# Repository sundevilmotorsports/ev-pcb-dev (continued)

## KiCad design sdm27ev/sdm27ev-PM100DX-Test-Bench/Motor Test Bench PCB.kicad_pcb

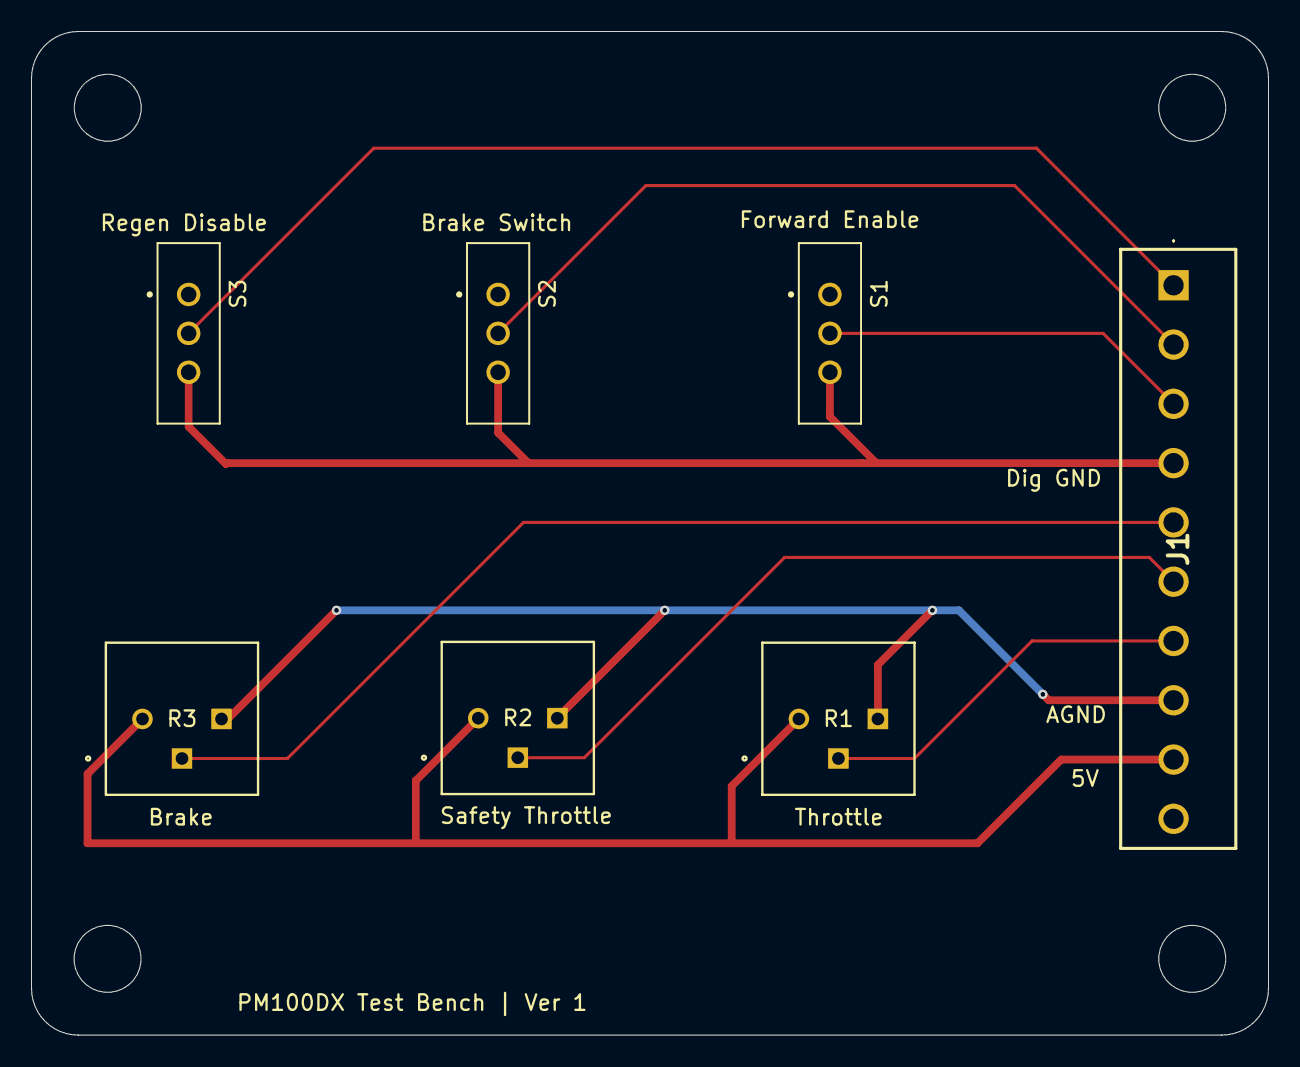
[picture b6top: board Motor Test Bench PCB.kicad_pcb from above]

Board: 2 copper layers, 79.5 x 64.5 mm, 7 parts (0 on the bottom side), 9 nets.

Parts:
J1: 20020327-D101B01LF; 20020327D101B01LF
R1: Throttle; POT_3386P
R2: Safety Throttle; POT_3386P
R3: Brake; POT_3386P
S1: Forward Enable; SW_EG1218
S2: Brake Switch; SW_EG1218
S3: Regen Disable; SW_EG1218

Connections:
5V: J1.9, R1.1, R2.1, R3.1
AGND: J1.8, R1.3, R2.3, R3.3
Brake Signal: J1.5, R3.2
Brake Switch: J1.2, S2.2
Digintal GND: J1.4, S1.3, S2.3, S3.3
Forward Enable: J1.3, S1.2
Regen Disable: J1.1, S3.2
Safety Throttle Signal: J1.6, R2.2
Throttle Signal: J1.7, R1.2

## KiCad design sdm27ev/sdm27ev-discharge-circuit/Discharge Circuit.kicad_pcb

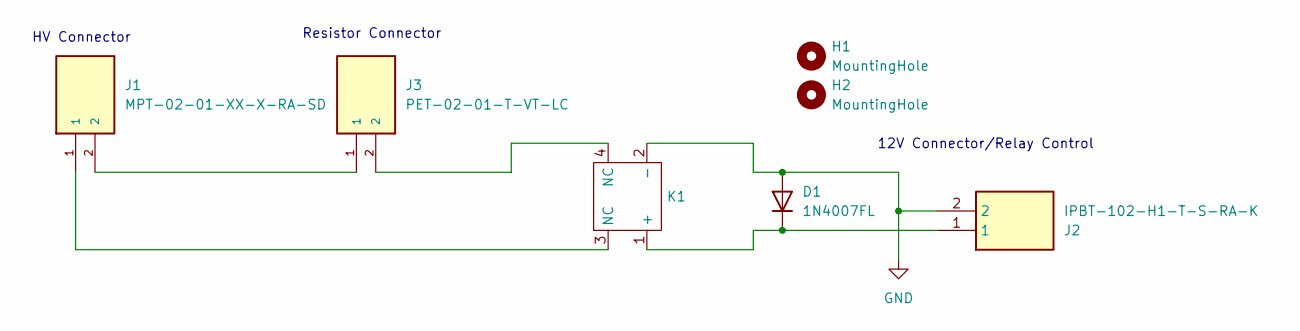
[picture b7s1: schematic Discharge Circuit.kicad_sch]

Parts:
D1: 1N4007FL; D_SOD-123F
H1, H2: MountingHole; MountingHole_3.2mm_M3
J1: MPT-02-01-XX-X-RA-SD; SAMTEC_MPT-02-01-XX-X-RA-SD; PARTREV B
J2: IPBT-102-H1-T-S-RA-K; IPBT102H1TSRAK; Mouser Part Number 200-IPBT102H1TSRAK
J3: PET-02-01-T-VT-LC; SAMTEC_PET-02-XX-X-VT-LC; PARTREV C
K1: S82405VHR

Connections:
GND: D1.2 (A), J2.2, K1.2 (-)
unnamed: D1.1 (K), J2.1, K1.1 (+)
unnamed: J1.1, K1.3 (NC)
unnamed: J1.2, J3.1
unnamed: J3.2, K1.4 (NC)

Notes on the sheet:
Resistor Connector
12V Connector/Relay Control
HV Connector

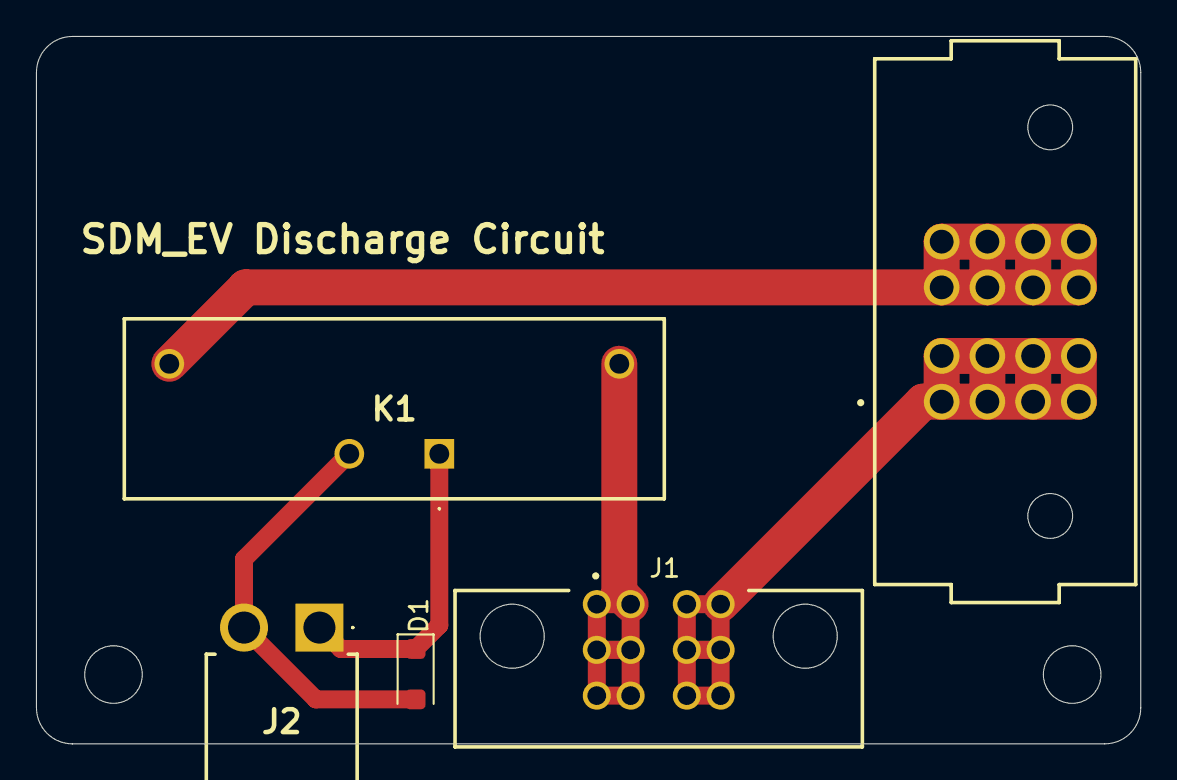
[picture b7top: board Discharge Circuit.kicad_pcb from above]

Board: 2 copper layers, 61.3 x 39.3 mm, 7 parts (0 on the bottom side), 5 nets.

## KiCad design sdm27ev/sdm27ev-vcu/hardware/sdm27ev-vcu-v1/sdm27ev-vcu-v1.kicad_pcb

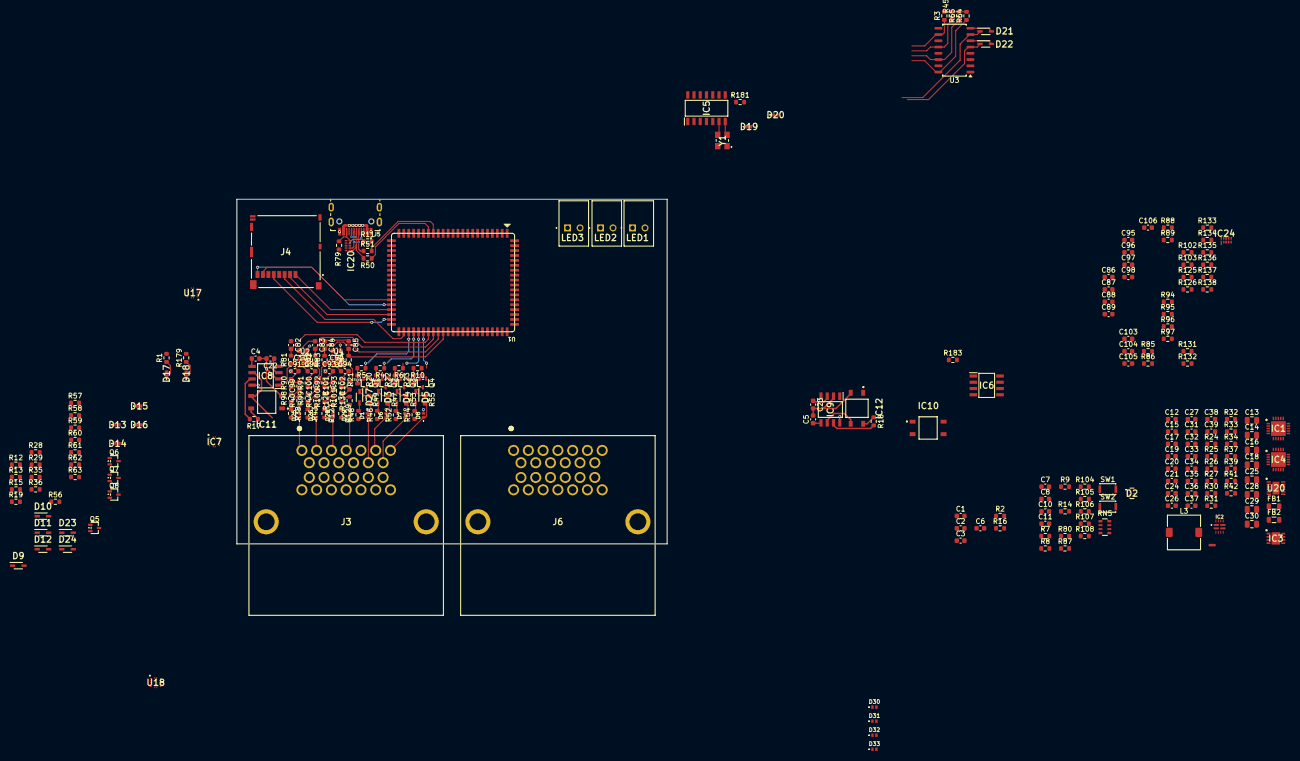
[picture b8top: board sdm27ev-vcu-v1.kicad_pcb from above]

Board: 2 copper layers, 87.4 x 70.0 mm, 253 parts (0 on the bottom side), 181 nets.

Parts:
C1, C2, C3, C4, C5, C6, C7, C11, C15, C17, C22, C23, C24, C26, C32, C34, C82, C83, C84, C85, C86, C87, C88, C89, C90, C107: 100nF; C_0603_1608Metric
C8, C19, C20, C21, C31, C33, C35, C36, C37, C38, C39: 1uF; C_0603_1608Metric
C10: 10uF; C_0603_1608Metric
C12: 10nF; C_0603_1608Metric
C13, C14, C16, C18: 10uF; C_0805_2012Metric
C25, C28: 4.7uF; C_0805_2012Metric
C27: 33pF; C_0603_1608Metric
C29, C30: 33uF; C_0805_2012Metric
C91, C92, C93, C94, C95, C96, C97, C98: 10n; C_0603_1608Metric
C99, C100, C101, C102, C103, C104, C105, C106: 20.5nF; C_0603_1608Metric
D1, D6, D7, D8, D25, D26, D28, D29, D30, D31, D32, D33: PESD24VL1BLS-QYL; PESD24VL1BLSQYL-Compact
D2: PUSB3FR6Z
D3, D4, D5, D9, D10, D11, D12, D21, D22, D23, D24, D27: BAT54WS-7-F; SOD2513X120N
D13, D14, D15, D16, D17, D18, D19, D20: PESD24VL1BLS-QYL; PESD24VL1BLSQYL
FB1, FB2: 600Ohm@100MHz ~1.4A; L_0805_2012Metric
IC1, IC4: MAX20087ATPB_VY+T; QFN50P400X400X80-21N-D
IC2: TPS2121RUXR
IC3: TLV76733QWDRBRQ1; SON65P300X300X100-9N-D
IC5: MCP2518FDT-E_SL; SOIC127P600X175-14N
IC6, IC8, IC9: TCAN3413DR; SOIC127P600X175-8N
IC7: TLV9064IRUCR; QFN40P200X200X40-14N
IC10, IC11, IC12: TLP175A_TPL,E; TLP266J
IC20, IC24: TPD4E05U06QDQARQ1; DQA_R-PUSON-N10_
J3, J6: 6437288-4; 64372884
J4: 2201778-1; 22017781
J5: USB4725-03-C-KIT; GCT_USB4730-GF-A_REVA
L3: 4.7uH; L_SXN_SMDRI62
LED1: RED; SSFLXH100LID01
LED2, LED3: GREEN; SSFLXH100LID01
NT1: NetTieGND; NetTie-2_SMD_Pad0.5mm
Q1, Q2, Q3, Q4, Q5, Q6, Q7, Q8: DMN62D2UWQ; SOT-323_SC-70
R1, R42, R46, R47, R48, R49, R52, R53, R54, R55, R56, R57, R58, R59, R60, R61, R62, R63, R179, R181, R183: 1k; R_0603_1608Metric
R2: 0; R_0603_1608Metric
R3, R45, R64, R65: 10K; R_0603_1608Metric
R4, R5, R6, R10, R12, R13, R15, R16, R17, R18, R19, R81, R82, R83, R84, R85, R86, R88, R89, R106, R107, R108: 100; R_0603_1608Metric
R7, R8, R9, R14, R38, R43, R80, R87, R104, R105, R127, R129, R131, R133, R135, R137: 10k; R_0603_1608Metric
R11, R79: 5.1k; R_0603_1608Metric
R20, R21, R22, R23, R28, R29, R35, R36, R41: 100k; R_0603_1608Metric
R24: 16.2; R_0603_1608Metric
R25, R27, R31: 5k; R_0603_1608Metric
R26, R30: 21k; R_0603_1608Metric
R32: 24.2k; R_0603_1608Metric
R33, R34: 25k; R_0603_1608Metric
R37: 34.8k; R_0603_1608Metric
R39: 19.1k; R_0603_1608Metric
R40, R44, R128, R130, R132, R134, R136, R138: 17.8K; R_0603_1608Metric
R50, R51: 27; R_0603_1608Metric
R90, R91, R92, R93, R94, R95, R96, R97: 6.49k; R_0603_1608Metric
R98, R99, R100, R101, R102, R103, R125, R126: 4.75k; R_0603_1608Metric
RN5: 10k; R_Array_Convex_4x0603
SW1, SW2: SW_Push; SW_SPST_CK_KXT3
U1: WT0132P4-A1
U2, U4: TLV9062xDSG; WSON-8-1EP_2x2mm_P0.5mm_EP0.9x1.6mm_ThermalVias
U3: TLP293-4; SOIC-16_4.55x10.3mm_P1.27mm
U17, U18: TLV9064IRUCR; QFN40P200X200X40-14N
U20: LMR51450FSQDRRRQ1; SON50P300X300X80-13N-D
Y1: ECS-3225MVQ-400-BS-TR; ECS3225MVQ400BSTR

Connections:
3.3V: C1.1, C2.1, C6.1, C7.1, C8.1, C13.1, C22.1, C23.1, C32.1, C34.1, FB1.1, IC1.11 (VDD), IC1.15 (EN), IC3.1 (OUT), IC3.3 (SNS), IC4.11 (VDD), IC4.15 (EN), IC4.16 (ADDR), IC5.14 (VDD), IC6.3 (VCC), IC8.3 (VCC), IC9.3 (VCC), J4.4 (VDD), R3.2, R7.2, R8.2, R9.2, R14.1, R45.2, R64.2, R65.2, R87.2, R104.2, R105.1, R106.1, R107.2, R108.2, Y1.1 (TRI-STATE), Y1.4 (VDD)
5V: C29.1, C30.1, FB2.1, IC2.7 (IN1), L3.2, R24.2, R26.2, R41.2, R42.2
12V: C25.1, C26.1, C28.1, R46.1, R48.1, R52.1, R54.1, R56.1, R57.1, R58.1, R59.1, U20.9 (EN), U20.10 (VIN), U20.11 (VIN_2), U20.12 (VIN_3)
/A1: C86.2, R85.2, U1.74 (GPIO16)
/A1IN: D25.1, J3.1, R38.2
/A2: C87.2, R86.2, U1.75 (GPIO17)
/A2IN: D26.1, J3.2, R43.2
/A3: C88.2, R88.2, U1.76 (GPIO18)
/A3IN: D28.1, J3.3, R127.2
/A4: C89.2, R89.2, U1.77 (GPIO19)
/A4IN: D29.1, J3.4, R129.2
/A5: C82.2, R81.2, U1.48 (GPIO49)
/A5IN: D30.1, IC24.1 (A5), R131.2
/A6: C83.2, R82.2, U1.49 (GPIO50)
/A6IN: D31.1, IC24.2 (A6), R133.2
/A7: C84.2, R83.2, U1.50 (GPIO51)
/A7IN: D32.1, IC24.4 (A7), R135.2
/A8: C85.2, R84.2, U1.51 (GPIO52)
/A8IN: D33.1, IC24.5 (A8), R137.2
/CAN1+: IC6.7 (CANH), R16.2
/CAN1-: IC6.6 (CANL), IC10.4
/CAN1_TERM: IC10.1, U1.72 (GPIO1)
/CAN2+: IC8.7 (CANH), R17.2
/CAN2-: IC8.6 (CANL), IC11.4
/CAN2_RX: IC8.4 (RXD), U1.52 (GPIO53)
/CAN2_TERM: IC11.1, U1.55 (GPIO2)
/CAN2_TX: IC8.1 (TXD), U1.54 (GPIO54)
/CAN3+: IC9.7 (CANH), R18.2
/CAN3-: IC9.6 (CANL), IC12.4
/CAN3_RX: IC9.4 (RXD), U1.65 (GPIO11)
/CAN3_TERM: IC12.1, U1.56 (GPIO3)
/CAN3_TX: IC9.1 (TXD), U1.63 (GPIO10)
/CAN/CAN1_RX: IC5.2 (RXCAN), IC6.4 (RXD)
/CAN/CAN1_STB: IC5.9 (~INT0/GPIO0/XSTBY), IC6.8 (STB), R2.2
/CAN/CAN1_TX: IC5.1 (TXCAN), IC6.1 (TXD)
/CAN_INT_1: IC5.4 (~INT), R14.2, U1.71 (GPIO0)
/CAN_SPI2_CS1: IC5.13 (NCS), U1.57 (GPIO4)
/CAN_SPI2_SCK: IC5.10 (SCK), U1.59 (GPIO6)
/CAN_SPI2_SDI: IC5.11 (SDI), U1.60 (GPIO7)
/CAN_SPI2_SDO: IC5.12 (SDO), U1.58 (GPIO5)
/DI1: R3.1, U1.69 (GPIO15), U3.10
/DI1IN: D17.1, R1.1
/DI2: R45.1, U1.68 (GPIO14), U3.12
/DI2IN: D18.1, R179.1
/DI3: R64.1, U1.66 (GPIO12), U3.16
/DI3IN: D19.1, R181.1
/DI4: R65.1, U1.67 (GPIO13), U3.14
/DI4IN: D20.1, R183.1
/DO1: R5.1, U1.44 (GPIO45)
/DO1IN: D1.1, J3.12, R49.2
/DO2: R4.1, U1.45 (GPIO46)
/DO2IN: D6.1, J3.6, R47.2
/DO3: R6.1, U1.46 (GPIO47)
/DO3IN: D7.1, J3.13, R53.2
/DO4: R10.1, U1.47 (GPIO48)
/DO4IN: D8.1, J3.7, R55.2
/DO5: R12.1, U1.24 (GPIO28)
/DO5IN: D13.1, R60.2
/DO6: R13.1, U1.25 (GPIO29)
/DO6IN: D14.1, R61.2
/DO7: R15.1, U1.26 (GPIO30)
/DO7IN: D15.1, R62.2
/DO8: R19.1, U1.27 (GPIO31)
/DO8IN: D16.1, R63.2
/ESP_LDO: R80.2, RN5.5 (R4.2), RN5.6 (R3.2), RN5.7 (R2.2), RN5.8 (R1.2), U1.32 (ESP_LDO_VO4)
/Power/A1_5V: C31.1, IC1.6 (OUT1)
/Power/A2_5V: C21.1, IC1.20 (OUT2)
/Power/A3_5V: C20.1, IC1.7 (OUT3)
/Power/A4_5V: C19.1, IC1.19 (OUT4)
/Power/A5_5V: C39.1, IC4.6 (OUT1)
/Power/A6_5V: C38.1, IC4.20 (OUT2)
/Power/A7_5V: C37.1, IC4.7 (OUT3)
/Power/A8_5V: C36.1, IC4.19 (OUT4)
/Power/SCL: IC1.14 (SCL), IC4.14 (SCL)
/Power/SDA: IC1.13 (SDA), IC4.13 (SDA)
/SD1-CLK: D2.4 (CLK), J4.5 (CLK), U1.40 (GPIO43)
/SD1-CMD: D2.5 (CMD), J4.3 (CMD), R80.1, U1.43 (GPIO44)
/SD1-DAT0: D2.1 (DAT0), J4.7 (DAT0), RN5.4 (R4.1), U1.36 (GPIO39)
/SD1-DAT1: D2.7 (DAT1), J4.8 (DAT1), RN5.3 (R3.1), U1.37 (GPIO40)
/SD1-DAT2: D2.6 (DAT2), J4.1 (DAT2), RN5.2 (R2.1), U1.38 (GPIO41)
/SD1-DAT3: D2.3 (DAT3), J4.2 (CD/DAT3), RN5.1 (R1.1), U1.39 (GPIO42)
/StatLED1: LED3.1 (K), U1.28 (GPIO32)
/StatLED2: LED2.1 (K), U1.29 (GPIO33)
/USB_D+: IC20.1 (A1), J5.A6 (D+), J5.B6 (D+), R50.2
/USB_D-: IC20.2 (A2), J5.A7 (D-), J5.B7 (D-), R51.1
A3.3V: C15.1, C16.1, C90.1, C107.1, FB1.2, U2.8 (V+), U4.8 (V+), U17.3 (V+), U18.3 (V+)
A5V: C17.1, C18.1, C33.1, C35.1, FB2.2, IC1.2 (IN), IC1.3 (IN_2), IC1.4 (IN_3), IC4.2 (IN), IC4.3 (IN_2), IC4.4 (IN_3)
GND: C1.2, C2.2, C3.2, C4.2, C5.2, C6.2, C7.2, C8.2, C10.2, C11.2, C12.2, C13.2, C14.2, C15.2, C16.2, C17.2, C18.2, C19.2, C20.2, C21.2, C22.2, C23.2, C25.2, C26.2, C28.2, C29.2, C30.2, C31.2, C32.2, C33.2, C34.2, C35.2, C36.2, C37.2, C38.2, C39.2, C82.1, C83.1, C84.1, C85.1, C86.1, C87.1, C88.1, C89.1, C90.2, C91.1, C92.1, C93.1, C94.1, C95.1, C96.1, C97.1, C98.1, C107.2, D1.2, D2.2 (GND), D6.2, D7.2, D8.2, D13.2, D14.2, D15.2, D16.2, D17.2, D18.2, D19.2, D20.2, D21.2 (A), D22.2 (A), D23.2 (A), D24.2 (A), D25.2, D26.2, D28.2, D29.2, D30.2, D31.2, D32.2, D33.2, IC1.1 (PGND_1), IC1.5 (PGND_2), IC1.9 (GND), IC1.12 (GND_2), IC1.16 (ADDR), IC1.21 (EP), IC2.3 (CP2), IC2.9 (ST), IC2.12 (GND), IC3.4 (GND), IC3.6 (GND_2), IC3.9 (EP), IC4.1 (PGND_1), IC4.5 (PGND_2), IC4.9 (GND), IC4.12 (GND_2), IC4.21 (EP), IC5.7 (VSS), IC6.2 (GND), IC8.2 (GND), IC8.8 (STB), IC9.2 (GND), IC9.8 (STB), IC10.3, IC11.3, IC12.3, IC20.3 (GND), IC20.8 (GND_2), IC24.3 (GND), IC24.8 (GND_2), J3.5, J3.9, J3.11, J4.6 (VSS), J4.11 (GND_1), J4.12 (GND_2), J4.13 (GND_3), J4.14 (GND_4), J4.15 (GND_5), J4.16 (GND_6), J5.A1 (GND), LED1.1 (K), NT1.1, Q1.2 (S), Q2.2 (S), Q3.2 (S), Q4.2 (S), Q5.2 (S), Q6.2 (S), Q7.2 (S), Q8.2 (S), R2.1, R11.2, R20.1, R21.1, R22.1, R23.1, R25.1, R27.1, R28.1, R29.1, R31.1, R32.1, R33.1, R34.1, R35.1, R36.1, R37.1, R40.1, R44.1, R79.2, R128.1, R130.1, R132.1, R134.1, R136.1, R138.1, SW1.1, SW2.2, U1.1 (GND), U1.8 (GND), U1.15 (GND), U1.18 (GND), U1.21 (GND), U1.42 (GND), U1.53 (GND), U1.64 (GND), U1.73 (GND), U1.82 (GND), U2.4 (V-), U2.9 (PAD), U3.2, U3.4, U3.6, U3.8, U3.9, U3.11, U3.13, U3.15, U4.4 (V-), U4.9 (PAD), U17.10 (V-), U18.10 (V-), U20.13 (PGND), Y1.2 (GND)
unnamed: C27.2, R42.1
unnamed: C99.1, R90.1, R98.2
unnamed: C100.1, R91.1, R99.2
unnamed: C101.1, R92.1, R100.2
unnamed: C102.1, R93.1, R101.2
unnamed: C103.1, R94.1, R102.2
unnamed: C104.1, R95.1, R103.2
unnamed: C105.1, R96.1, R125.2
unnamed: C106.1, R97.1, R126.2
unnamed: D3.2 (A), R46.2
unnamed: D3.1 (K), Q2.3 (D), R47.1
unnamed: D4.2 (A), R52.2
unnamed: D4.1 (K), Q3.3 (D), R53.1
unnamed: D5.2 (A), R54.2
unnamed: D5.1 (K), Q4.3 (D), R55.1
unnamed: D9.2 (A), R56.2
unnamed: D9.1 (K), Q5.3 (D), R60.1
unnamed: D10.2 (A), R57.2
unnamed: D10.1 (K), Q6.3 (D), R61.1
unnamed: D11.2 (A), R58.2
unnamed: D11.1 (K), Q7.3 (D), R62.1
unnamed: D12.2 (A), R59.2
unnamed: D12.1 (K), Q8.3 (D), R63.1
unnamed: D21.1 (K), R1.2, U3.7
unnamed: D22.1 (K), R179.2, U3.5
unnamed: D23.1 (K), R181.2, U3.1
unnamed: D24.1 (K), R183.2, U3.3
unnamed: D27.2 (A), R48.2
unnamed: D27.1 (K), Q1.3 (D), R49.1
unnamed: IC1.10 (ISET), R33.2
unnamed: IC2.10 (ILIM), R32.2
unnamed: IC2.5 (OV1), R26.1, R27.2
unnamed: IC2.4 (OV2), R30.1, R31.2
unnamed: IC2.6 (PR1), R24.1, R25.2
unnamed: C12.1, IC2.11 (SS)
unnamed: IC4.10 (ISET), R34.2
unnamed: IC5.6 (OSC1), Y1.3 (OUTPUT)
unnamed: C3.1, IC6.5 (V_IO)
unnamed: C4.1, IC8.5 (V_IO)
unnamed: C5.1, IC9.5 (V_IO)
unnamed: IC10.6, R16.1
unnamed: IC11.6, R17.1
unnamed: IC12.6, R18.1
unnamed: IC20.4 (A3), J5.A5 (CC1), R11.1
unnamed: IC20.5 (A4), J5.B5 (CC2), R79.1
unnamed: IC20.6 (NC_4), IC20.7 (NC_1), IC20.9 (NC_2), IC20.10 (NC_3)
unnamed: IC24.6 (NC_4), IC24.7 (NC_1), IC24.9 (NC_2), IC24.10 (NC_3)
unnamed: LED1.2 (A), R106.2
unnamed: LED2.2 (A), R107.1
unnamed: LED3.2 (A), R108.1
unnamed: Q1.1 (G), R5.2, R21.2
unnamed: Q2.1 (G), R4.2, R20.2
unnamed: Q3.1 (G), R6.2, R22.2
unnamed: Q4.1 (G), R10.2, R23.2
unnamed: Q5.1 (G), R12.2, R28.2
unnamed: Q6.1 (G), R13.2, R29.2
unnamed: Q7.1 (G), R15.2, R35.2
unnamed: Q8.1 (G), R19.2, R36.2
unnamed: R38.1, R40.2, R98.1
unnamed: R43.1, R44.2, R99.1
unnamed: R100.1, R127.1, R128.2
unnamed: R101.1, R129.1, R130.2
unnamed: R102.1, R131.1, R132.2
unnamed: R103.1, R133.1, R134.2
unnamed: R125.1, R135.1, R136.2
unnamed: R126.1, R137.1, R138.2
unnamed: R8.1, R9.1, SW1.2, SW2.1, U1.31 (GPIO35), U1.70 (CHIP_PU)
unnamed: R7.1, U1.33 (GPIO36)
unnamed: R51.2, U1.16 (USB_DM)
unnamed: R50.1, U1.17 (USB_DP)
unnamed: C91.2, R90.2, U2.3 (+)
unnamed: C99.2, R81.1, U2.1, U2.2 (-)
unnamed: C92.2, R91.2, U2.5 (+)
unnamed: C100.2, R82.1, U2.6 (-), U2.7
unnamed: C93.2, R92.2, U4.3 (+)
unnamed: C101.2, R83.1, U4.1, U4.2 (-)
unnamed: C94.2, R93.2, U4.5 (+)
unnamed: C102.2, R84.1, U4.6 (-), U4.7
unnamed: C95.2, R94.2, U18.1 (IN1+)
unnamed: C103.2, R85.1, U18.2 (IN1-), U18.14 (OUT1)
unnamed: C96.2, R95.2, U18.4 (IN2+)
unnamed: C104.2, R86.1, U18.5 (IN2-), U18.6 (OUT2)
unnamed: C97.2, R96.2, U18.9 (IN3+)
unnamed: C105.2, R88.1, U18.7 (OUT3), U18.8 (IN3-)
unnamed: C98.2, R97.2, U18.11 (IN4+)
unnamed: C106.2, R89.1, U18.12 (IN4-), U18.13 (OUT4)
unnamed: NT1.2, R39.1, U20.8 (AGND)
unnamed: C24.1, U20.4 (BOOT)
unnamed: C27.1, R39.2, R41.1, U20.7 (FB)
unnamed: R37.2, U20.6 (RT)
unnamed: C24.2, L3.1, U20.1 (SW), U20.2 (SW_2), U20.3 (SW_3)
VBUS: IC2.2 (IN2), J5.A4 (VBUS), R30.2
VCC: C10.1, C11.1, C14.1, IC2.1 (OUT_1), IC2.8 (OUT_2), IC3.5 (EN), IC3.8 (IN), U1.41 (VCC)
